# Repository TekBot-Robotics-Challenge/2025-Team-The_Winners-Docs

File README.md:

# TheWInners_Doc
Documentation des travaux de l'équipe les WInners participant à la TRC2025. 

## 🚀 Step-by-Step Getting Started Guide

### Step 1: Clone and Install

First, clone the repository and install dependencies:

```bash
# Clone the repository
git clone https://github.com/Marzoukath/TheWInners_Doc.git
cd TheWInners_Doc

# Install dependencies
yarn install

# Start development server
yarn dev
```

Your site will be available at `http://localhost:4321`

### Step 2: Configure Your Site

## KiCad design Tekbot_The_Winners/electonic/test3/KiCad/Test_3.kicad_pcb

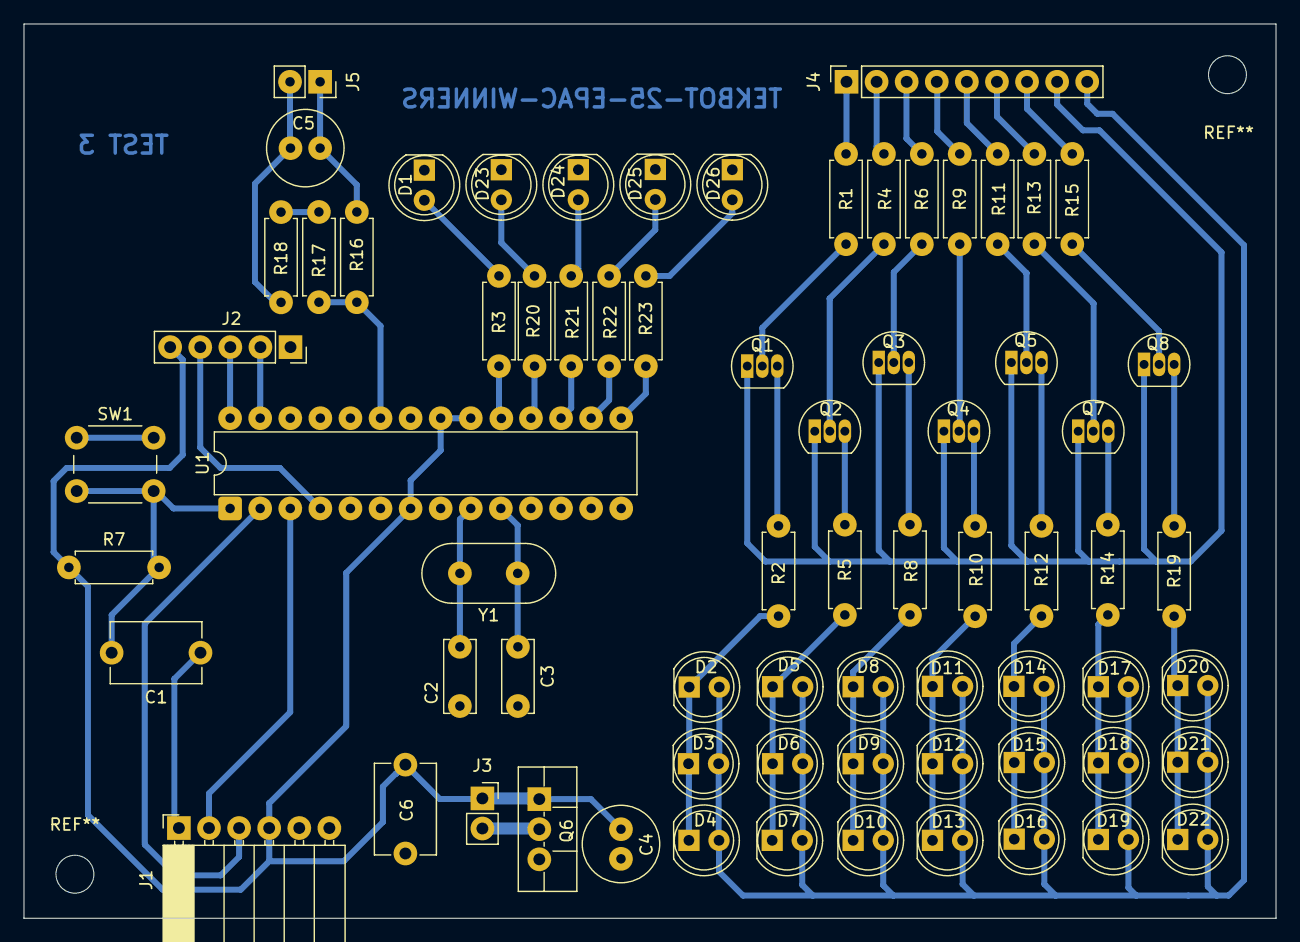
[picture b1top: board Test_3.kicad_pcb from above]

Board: 2 copper layers, 105.7 x 75.5 mm, 71 parts (0 on the bottom side), 56 nets.

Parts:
C1: 100nF; C_Disc_D7.5mm_W5.0mm_P7.50mm
C2, C3: 22pF; C_Disc_D6.0mm_W2.5mm_P5.00mm
C4, C5: 470µF; C_Radial_D6.3mm_H5.0mm_P2.50mm
C6: 100n; C_Disc_D7.5mm_W5.0mm_P7.50mm
D1, D2, D3, D4, D5, D6, D7, D8, D9, D10, D11, D12, D13, D14, D15, D16, D17, D18, D19, D20, D21, D22, D23, D24, D25, D26: LED; LED_D5.0mm
J1: Prog_connector; PinSocket_1x06_P2.54mm_Horizontal
J2: Conn_01x05_Pin; PinSocket_1x05_P2.54mm_Vertical
J3: 5V_power_Pins; PinSocket_1x02_P2.54mm_Vertical
J4: LED_pwm_connector; PinSocket_1x09_P2.54mm_Vertical
J5: Batt_connector; PinSocket_1x02_P2.54mm_Vertical
Q1, Q2, Q3, Q4, Q5, Q7, Q8: 2N2219; TO-92_Inline
Q6: NMOS; TO-220F-3_Vertical
R1, R2, R4, R5, R6, R8, R9, R10, R11, R12, R13, R14, R15, R19, R20, R21, R22, R23: R; R_Axial_DIN0207_L6.3mm_D2.5mm_P7.62mm_Horizontal
R3: 220; R_Axial_DIN0207_L6.3mm_D2.5mm_P7.62mm_Horizontal
R7, R16, R17: 10k; R_Axial_DIN0207_L6.3mm_D2.5mm_P7.62mm_Horizontal
R18: 4.7k; R_Axial_DIN0207_L6.3mm_D2.5mm_P7.62mm_Horizontal
SW1: SW_Push; SW_PUSH_6mm
U1: ATmega328-P; DIP-28_W7.62mm
Y1: Crystal; Crystal_HC49-U_Vertical

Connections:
/B+: C5.1, J5.1, R16.1
/B-: C5.2, J5.2, R18.2
/L_GND: J4.8, Q1.1 (E), Q2.1 (E), Q3.1 (E), Q4.1 (E), Q5.1 (E), Q7.1 (E), Q8.1 (E)
/L_Vcc: D2.2 (A), D3.2 (A), D4.2 (A), D5.2 (A), D6.2 (A), D7.2 (A), D8.2 (A), D9.2 (A), D10.2 (A), D11.2 (A), D12.2 (A), D13.2 (A), D14.2 (A), D15.2 (A), D16.2 (A), D17.2 (A), D18.2 (A), D19.2 (A), D20.2 (A), D21.2 (A), D22.2 (A), J4.9
/sg1: J4.1, R1.1
/sg2: J4.2, R4.1
/sg3: J4.3, R6.1
/sg4: J4.4, R9.1
/sg5: J4.5, R11.1
/sg6: J4.6, R13.1
/sg7: J4.7, R15.1
A0: R16.2, R17.1, U1.23 (PC0)
GND: J3.2, Q6.2 (D)
L-25: R23.1, U1.15 (PB1)
L-50: R22.1, U1.16 (PB2)
L-75: R21.1, U1.17 (PB3)
L-100: R20.1, U1.18 (PB4)
Lbuilt: R3.1, U1.19 (PB5)
unnamed: D1.2 (A), R3.2
unnamed: D2.1 (K), D3.1 (K), D4.1 (K), R2.2
unnamed: D5.1 (K), D6.1 (K), D7.1 (K), R5.2
unnamed: D8.1 (K), D9.1 (K), D10.1 (K), R8.2
unnamed: D11.1 (K), D12.1 (K), D13.1 (K), R10.2
unnamed: D14.1 (K), D15.1 (K), D16.1 (K), R12.2
unnamed: D17.1 (K), D18.1 (K), D19.1 (K), R14.2
unnamed: D20.1 (K), D21.1 (K), D22.1 (K), R19.2
unnamed: D23.2 (A), R20.2
unnamed: D24.2 (A), R21.2
unnamed: D25.2 (A), R22.2
unnamed: D26.2 (A), R23.2
unnamed: C1.1, J1.1
unnamed: Q1.2 (B), R1.2
unnamed: Q1.3 (C), R2.1
unnamed: Q2.2 (B), R4.2
unnamed: Q2.3 (C), R5.1
unnamed: Q3.2 (B), R6.2
unnamed: Q3.3 (C), R8.1
unnamed: Q4.2 (B), R9.2
unnamed: Q4.3 (C), R10.1
unnamed: Q5.2 (B), R11.2
unnamed: Q5.3 (C), R12.1
unnamed: Q7.2 (B), R13.2
unnamed: Q7.3 (C), R14.1
unnamed: Q8.2 (B), R15.2
unnamed: Q8.3 (C), R19.1
unnamed: R17.2, R18.1
OE: J2.4, U1.4 (PD2)
RST: C1.2, R7.2, SW1.2, U1.1 (~RESET/PC6)
Rx: J1.2, U1.3 (PD1)
SCL: J2.3, U1.28 (PC5)
SDA: J2.2, U1.27 (PC4)
Tx: J1.3, U1.2 (PD0)
V+: C4.1, C6.1, J1.4, J2.5, J3.1, Q6.1 (G), R7.1, U1.7 (VCC), U1.20 (AVCC), U1.21 (AREF)
V-: C2.2, C3.2, C4.2, C6.2, D1.1 (K), D23.1 (K), D24.1 (K), D25.1 (K), D26.1 (K), J1.6, J2.1, Q6.3 (S), SW1.1, U1.8 (GND), U1.22 (GND)
XTAL1: C2.1, U1.9 (XTAL1/PB6), Y1.2
XTAL2: C3.1, U1.10 (XTAL2/PB7), Y1.1

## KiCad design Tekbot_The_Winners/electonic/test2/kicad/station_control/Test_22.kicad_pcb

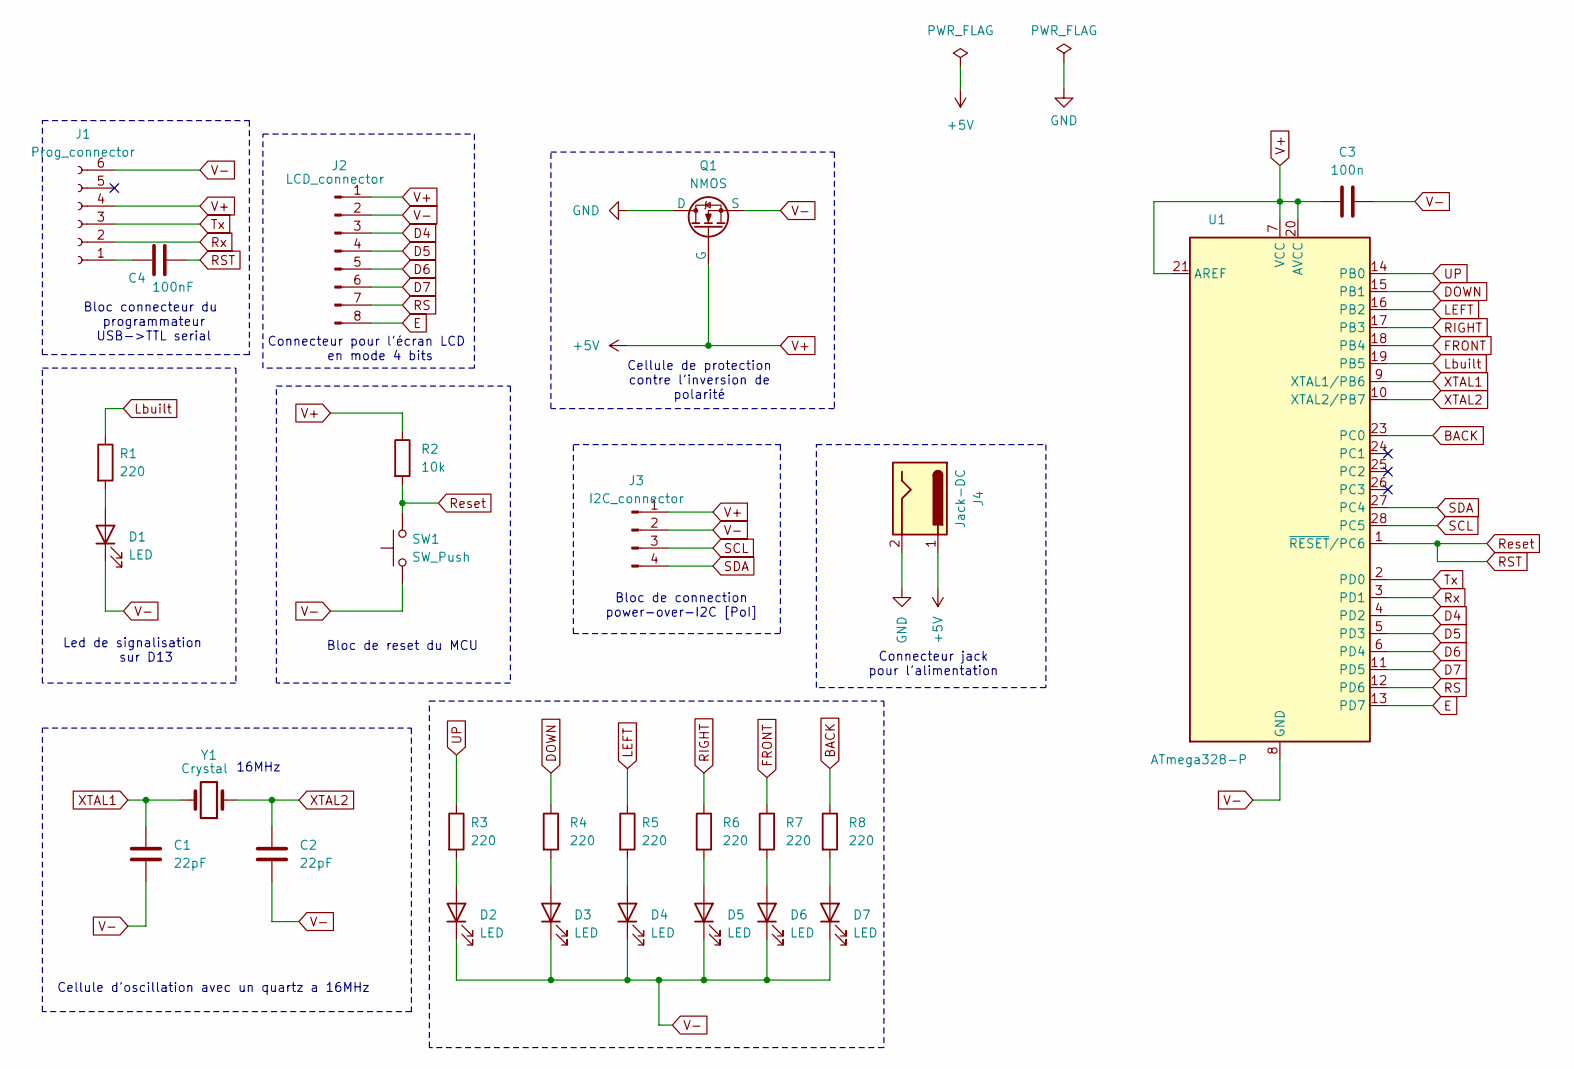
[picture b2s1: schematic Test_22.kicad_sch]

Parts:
C1, C2: 22pF; C_Disc_D7.5mm_W5.0mm_P7.50mm
C3: 100n; C_Disc_D7.5mm_W5.0mm_P7.50mm
C4: 100nF; C_Disc_D7.5mm_W5.0mm_P7.50mm
D1, D2, D3, D4, D5, D6, D7: LED; LED_D3.0mm
J1: Prog_connector; PinSocket_1x06_P2.54mm_Horizontal
J2: LCD_connector; PinSocket_1x08_P2.54mm_Vertical
J3: I2C_connector; JST_EH_S4B-EH_1x04_P2.50mm_Horizontal
J4: Jack-DC; BarrelJack_Horizontal
Q1: NMOS; TO-220F-3_Vertical
R1, R3, R4, R5, R6, R7, R8: 220; R_Axial_DIN0207_L6.3mm_D2.5mm_P7.62mm_Horizontal
R2: 10k; R_Axial_DIN0207_L6.3mm_D2.5mm_P7.62mm_Horizontal
SW1: SW_Push; SW_PUSH_6mm
U1: ATmega328-P; DIP-28_W7.62mm
Y1: Crystal; Crystal_HC49-U_Vertical

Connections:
BACK: R8.1, U1.23 (PC0)
D4: J2.3, U1.4 (PD2)
D5: J2.4, U1.5 (PD3)
D6: J2.5, U1.6 (PD4)
D7: J2.6, U1.11 (PD5)
DOWN: R4.1, U1.15 (PB1)
E: J2.8, U1.13 (PD7)
FRONT: R7.1, U1.18 (PB4)
GND: J4.2, Q1.1 (D)
LEFT: R5.1, U1.16 (PB2)
Lbuilt: R1.1, U1.19 (PB5)
unnamed: D1.2 (A), R1.2
unnamed: D2.2 (A), R3.2
unnamed: D3.2 (A), R4.2
unnamed: D4.2 (A), R5.2
unnamed: D5.2 (A), R6.2
unnamed: D6.2 (A), R7.2
unnamed: D7.2 (A), R8.2
unnamed: C4.1, J1.1
RIGHT: R6.1, U1.17 (PB3)
RS: J2.7, U1.12 (PD6)
RST: C4.2, R2.2, SW1.2, U1.1 (~RESET/PC6)
Rx: J1.2, U1.3 (PD1)
SCL: J3.3, U1.28 (PC5)
SDA: J3.4, U1.27 (PC4)
Tx: J1.3, U1.2 (PD0)
UP: R3.1, U1.14 (PB0)
V+: C3.1, J1.4, J2.1, J3.1, J4.1, Q1.2 (G), R2.1, U1.7 (VCC), U1.20 (AVCC), U1.21 (AREF)
V-: C1.2, C2.2, C3.2, D1.1 (K), D2.1 (K), D3.1 (K), D4.1 (K), D5.1 (K), D6.1 (K), D7.1 (K), J1.6, J2.2, J3.2, Q1.3 (S), SW1.1, U1.8 (GND), U1.22 (GND)
XTAL1: C1.1, U1.9 (XTAL1/PB6), Y1.2
XTAL2: C2.1, U1.10 (XTAL2/PB7), Y1.1

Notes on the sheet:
16MHz
Bloc connecteur du programmateur USB->TTL serial
Bloc de reset du MCU
Bloc de connection power-over-I2C [PoI]
Led de signalisation sur D13
Cellule d'oscillation avec un quartz a 16MHz
Connecteur jack pour l'alimentation
Cellule de protection contre l'inversion de polarité
Connecteur pour l'écran LCD en mode 4 bits

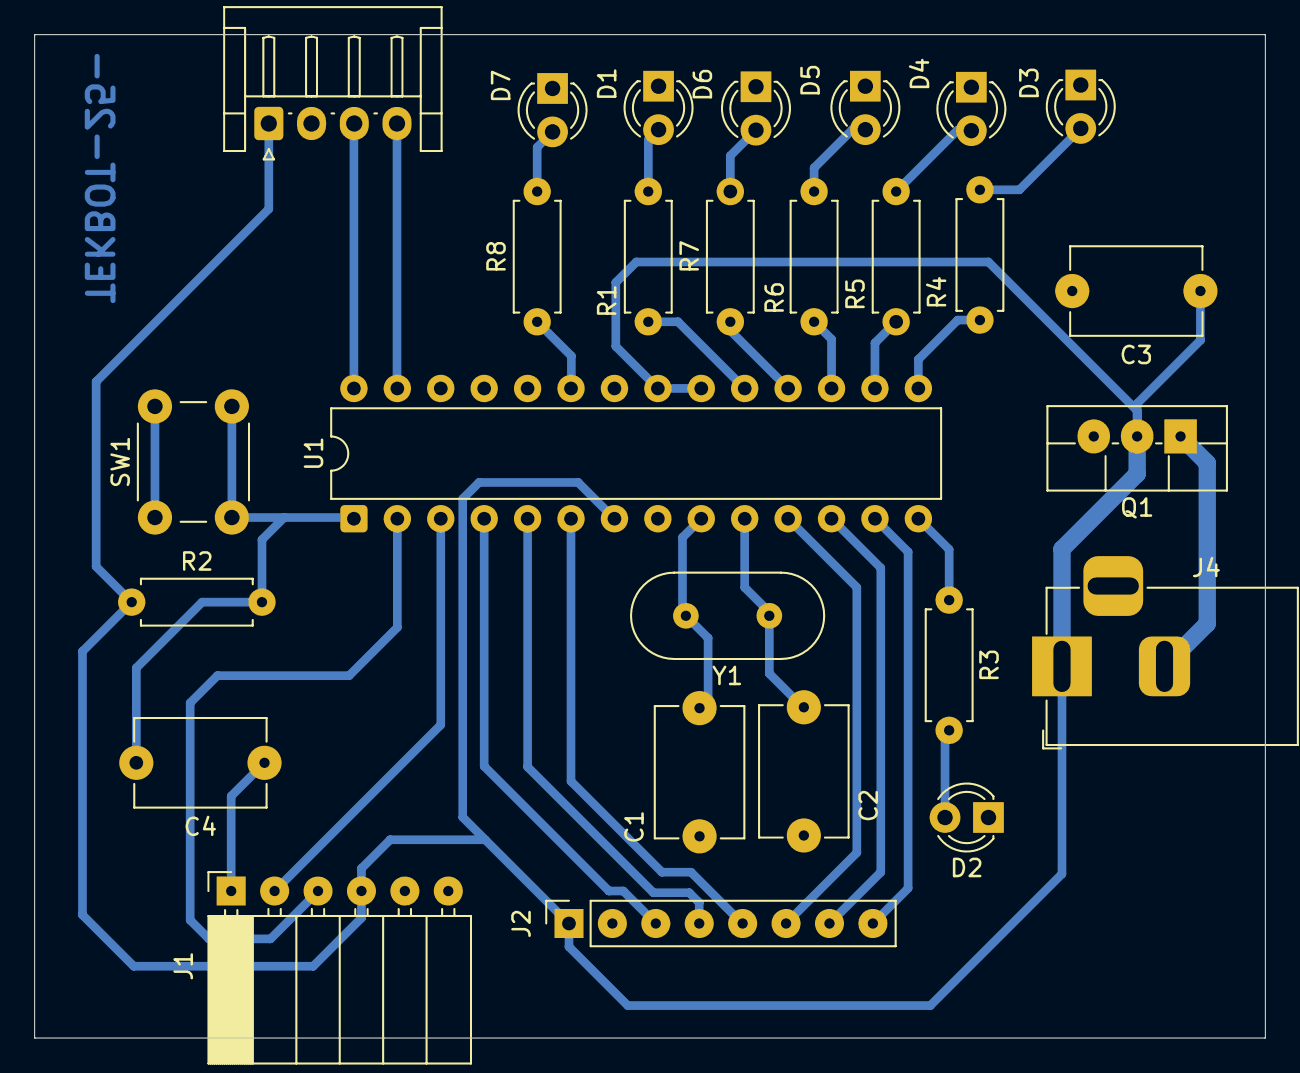
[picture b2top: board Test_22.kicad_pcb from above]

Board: 2 copper layers, 72.0 x 58.7 mm, 27 parts (0 on the bottom side), 31 nets.

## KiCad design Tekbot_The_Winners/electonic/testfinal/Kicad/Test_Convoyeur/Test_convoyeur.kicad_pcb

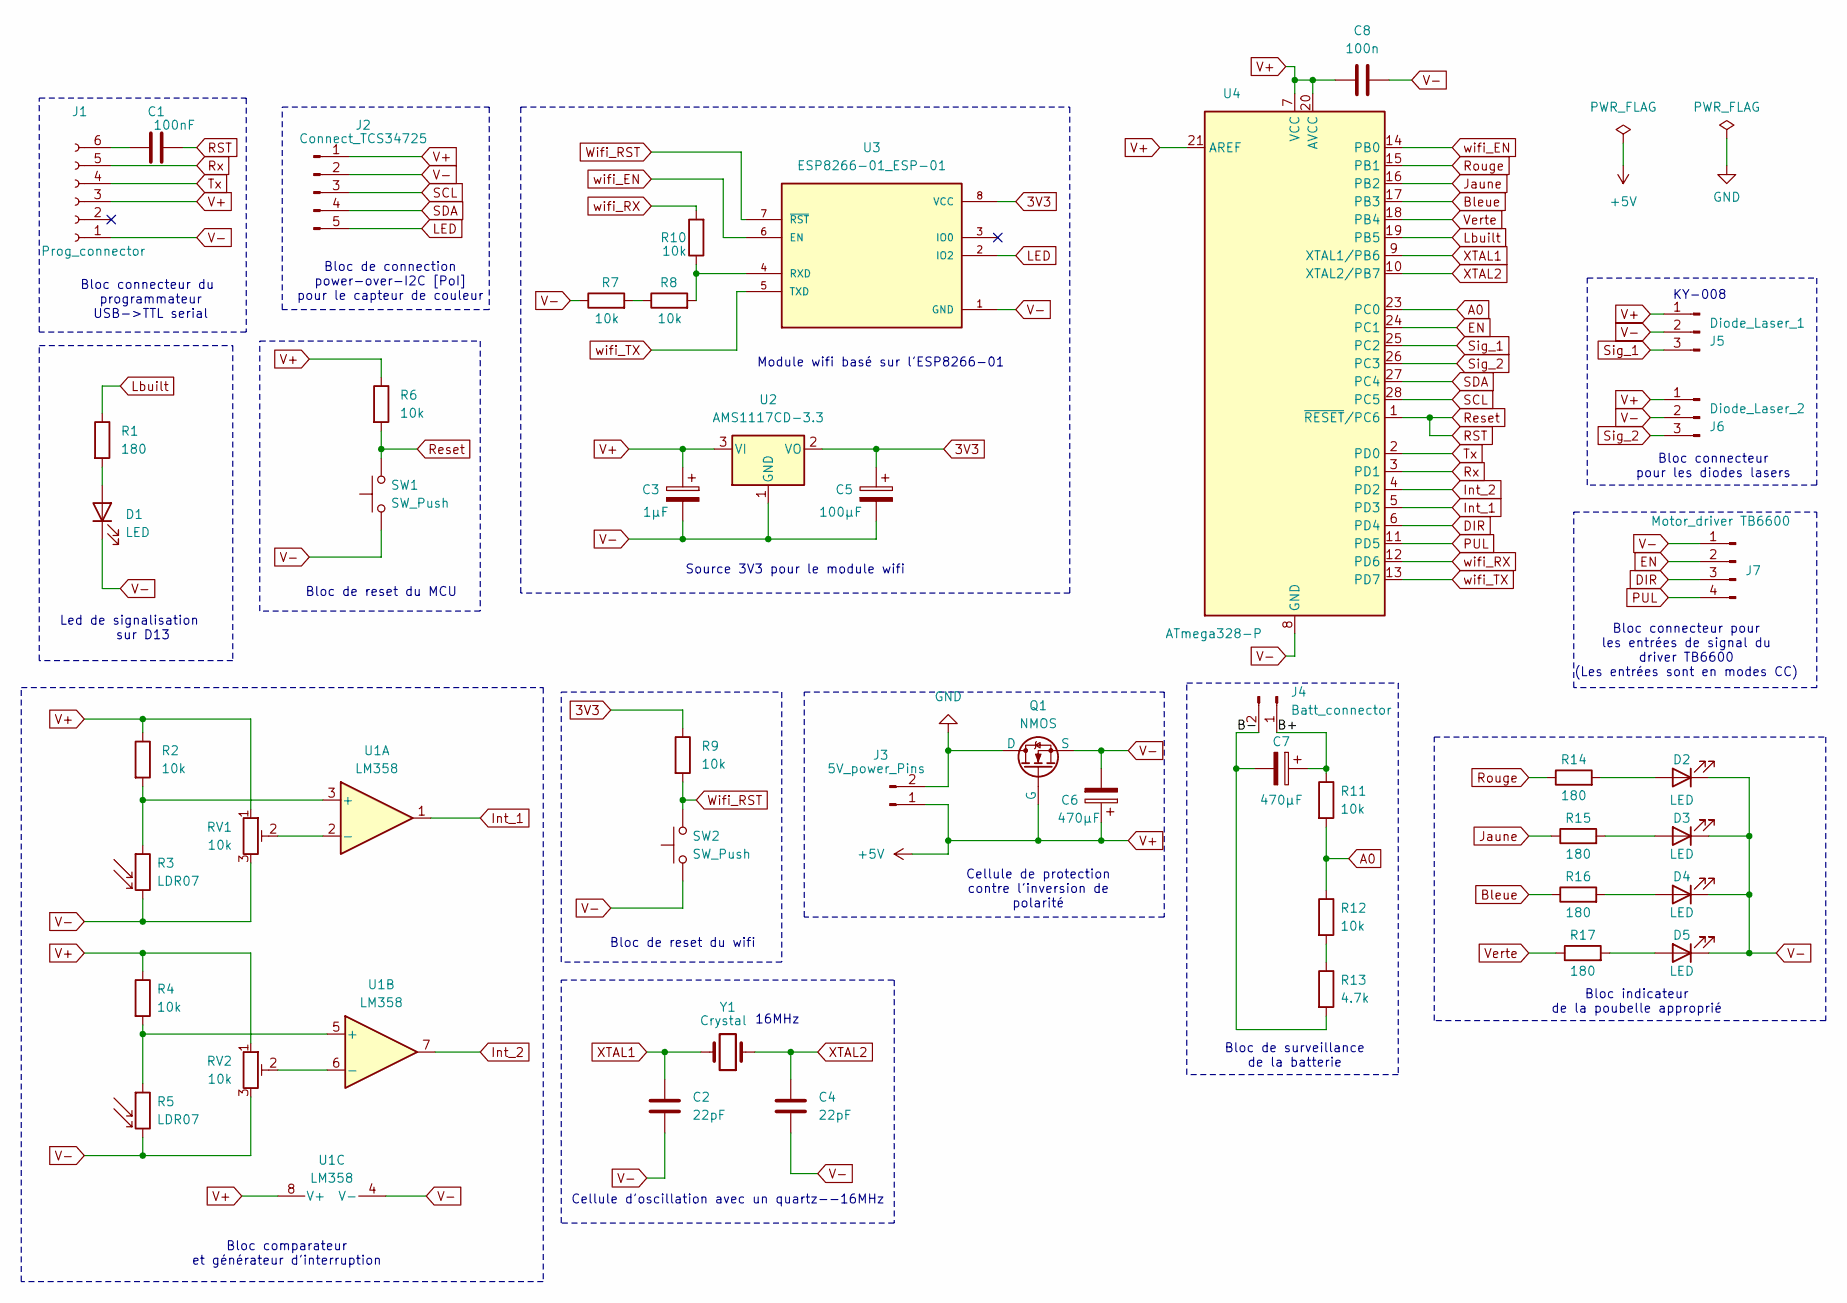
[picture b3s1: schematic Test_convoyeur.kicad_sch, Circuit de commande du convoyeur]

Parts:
C1: 100nF; C_Disc_D7.5mm_W5.0mm_P7.50mm
C2, C4: 22pF; C_Disc_D6.0mm_W2.5mm_P5.00mm
C3: 1µF; C_Radial_D6.3mm_H5.0mm_P2.50mm
C5: 100µF; C_Radial_D6.3mm_H5.0mm_P2.50mm
C6, C7: 470µF; C_Radial_D6.3mm_H5.0mm_P2.50mm
C8: 100n; C_Disc_D7.5mm_W5.0mm_P7.50mm
D1, D2, D3, D4, D5: LED; LED_D5.0mm
J1: Prog_connector; PinSocket_1x06_P2.54mm_Horizontal
J2: Connect_TCS34725; PinSocket_1x05_P2.54mm_Vertical
J3: 5V_power_Pins; PinSocket_1x02_P2.54mm_Vertical
J4: Batt_connector; PinSocket_1x02_P2.54mm_Vertical
J5: Diode_Laser_1; PinSocket_1x03_P2.54mm_Vertical
J6: Diode_Laser_2; PinSocket_1x03_P2.54mm_Vertical
J7: Motor_driver TB6600; PinHeader_1x04_P2.54mm_Vertical
Q1: NMOS; TO-220F-3_Vertical
R1, R14, R15, R16, R17: 180; R_Axial_DIN0207_L6.3mm_D2.5mm_P10.16mm_Horizontal
R2, R4, R6, R7, R8, R9, R10, R11, R12: 10k; R_Axial_DIN0207_L6.3mm_D2.5mm_P10.16mm_Horizontal
R3, R5: LDR07; R_LDR_5.1x4.3mm_P3.4mm_Vertical
R13: 4.7k; R_Axial_DIN0207_L6.3mm_D2.5mm_P10.16mm_Horizontal
RV1, RV2: 10k; R_ajustable
SW1, SW2: SW_Push; SW_PUSH_6mm
U1: LM358; DIP-8_W7.62mm
U2: AMS1117CD-3.3; TO-252-3_TabPin2
U3: ESP8266-01_ESP-01; XCVR_ESP8266-01_ESP-01; PARTREV V1.2
U4: ATmega328-P; DIP-28_W7.62mm
Y1: Crystal; Crystal_HC49-U_Vertical

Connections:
3V3: C5.1, R9.1, U2.2 (VO), U3.8 (VCC)
/B+: C7.1, J4.1, R11.1
/B-: C7.2, J4.2, R13.2
A0: R11.2, R12.1, U4.23 (PC0)
Bleue: R16.1, U4.17 (PB3)
DIR: J7.3, U4.6 (PD4)
EN: J7.2, U4.24 (PC1)
GND: J3.2, Q1.2 (D)
Int_1: U1.1, U4.5 (PD3)
Int_2: U1.7, U4.4 (PD2)
Jaune: R15.1, U4.16 (PB2)
LED: J2.5, U3.2 (IO2)
Lbuilt: R1.1, U4.19 (PB5)
unnamed: D1.2 (A), R1.2
unnamed: D2.2 (A), R14.2
unnamed: D3.2 (A), R15.2
unnamed: D4.2 (A), R16.2
unnamed: D5.2 (A), R17.2
unnamed: C1.1, J1.6
unnamed: R7.2, R8.1
unnamed: R12.2, R13.1
unnamed: R2.2, R3.1, U1.3 (+)
unnamed: RV1.2, U1.2 (-)
unnamed: R4.2, R5.1, U1.5 (+)
unnamed: RV2.2, U1.6 (-)
unnamed: R8.2, R10.1, U3.4 (RXD)
PUL: J7.4, U4.11 (PD5)
RST: C1.2, R6.2, SW1.2, U4.1 (~RESET/PC6)
Rouge: R14.1, U4.15 (PB1)
Rx: J1.5, U4.3 (PD1)
SCL: J2.3, U4.28 (PC5)
SDA: J2.4, U4.27 (PC4)
Sig_1: J5.3, U4.25 (PC2)
Sig_2: J6.3, U4.26 (PC3)
Tx: J1.4, U4.2 (PD0)
V+: C3.1, C6.1, C8.1, J1.3, J2.1, J3.1, J5.1, J6.1, Q1.1 (G), R2.1, R4.1, R6.1, RV1.1, RV2.1, U1.8 (V+), U2.3 (VI), U4.7 (VCC), U4.20 (AVCC), U4.21 (AREF)
V-: C2.2, C3.2, C4.2, C5.2, C6.2, C8.2, D1.1 (K), D2.1 (K), D3.1 (K), D4.1 (K), D5.1 (K), J1.1, J2.2, J5.2, J6.2, J7.1, Q1.3 (S), R3.2, R5.2, R7.1, RV1.3, RV2.3, SW1.1, SW2.1, U1.4 (V-), U2.1 (GND), U3.1 (GND), U4.8 (GND), U4.22 (GND)
Verte: R17.1, U4.18 (PB4)
Wifi_RST: R9.2, SW2.2, U3.7 (~RST)
XTAL1: C2.1, U4.9 (XTAL1/PB6), Y1.2
XTAL2: C4.1, U4.10 (XTAL2/PB7), Y1.1
wifi_EN: U3.6 (EN), U4.14 (PB0)
wifi_RX: R10.2, U4.12 (PD6)
wifi_TX: U3.5 (TXD), U4.13 (PD7)

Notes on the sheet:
Cellule de protection contre l'inversion de polarité
Bloc de reset du MCU
Bloc connecteur pour les entrées de signal du driver TB6600 (Les entrées sont en modes CC)
Bloc comparateur et générateur d'interruption
Source 3V3 pour le module wifi
Bloc indicateur de la poubelle approprié
Bloc de reset du wifi
Module wifi basé sur l'ESP8266-01
16MHz
KY-008
Bloc de surveillance de la batterie
Led de signalisation sur D13
Bloc connecteur pour les diodes lasers
Bloc de connection power-over-I2C [PoI] pour le capteur de couleur
Bloc connecteur du programmateur USB->TTL serial
Cellule d'oscillation avec un quartz--16MHz

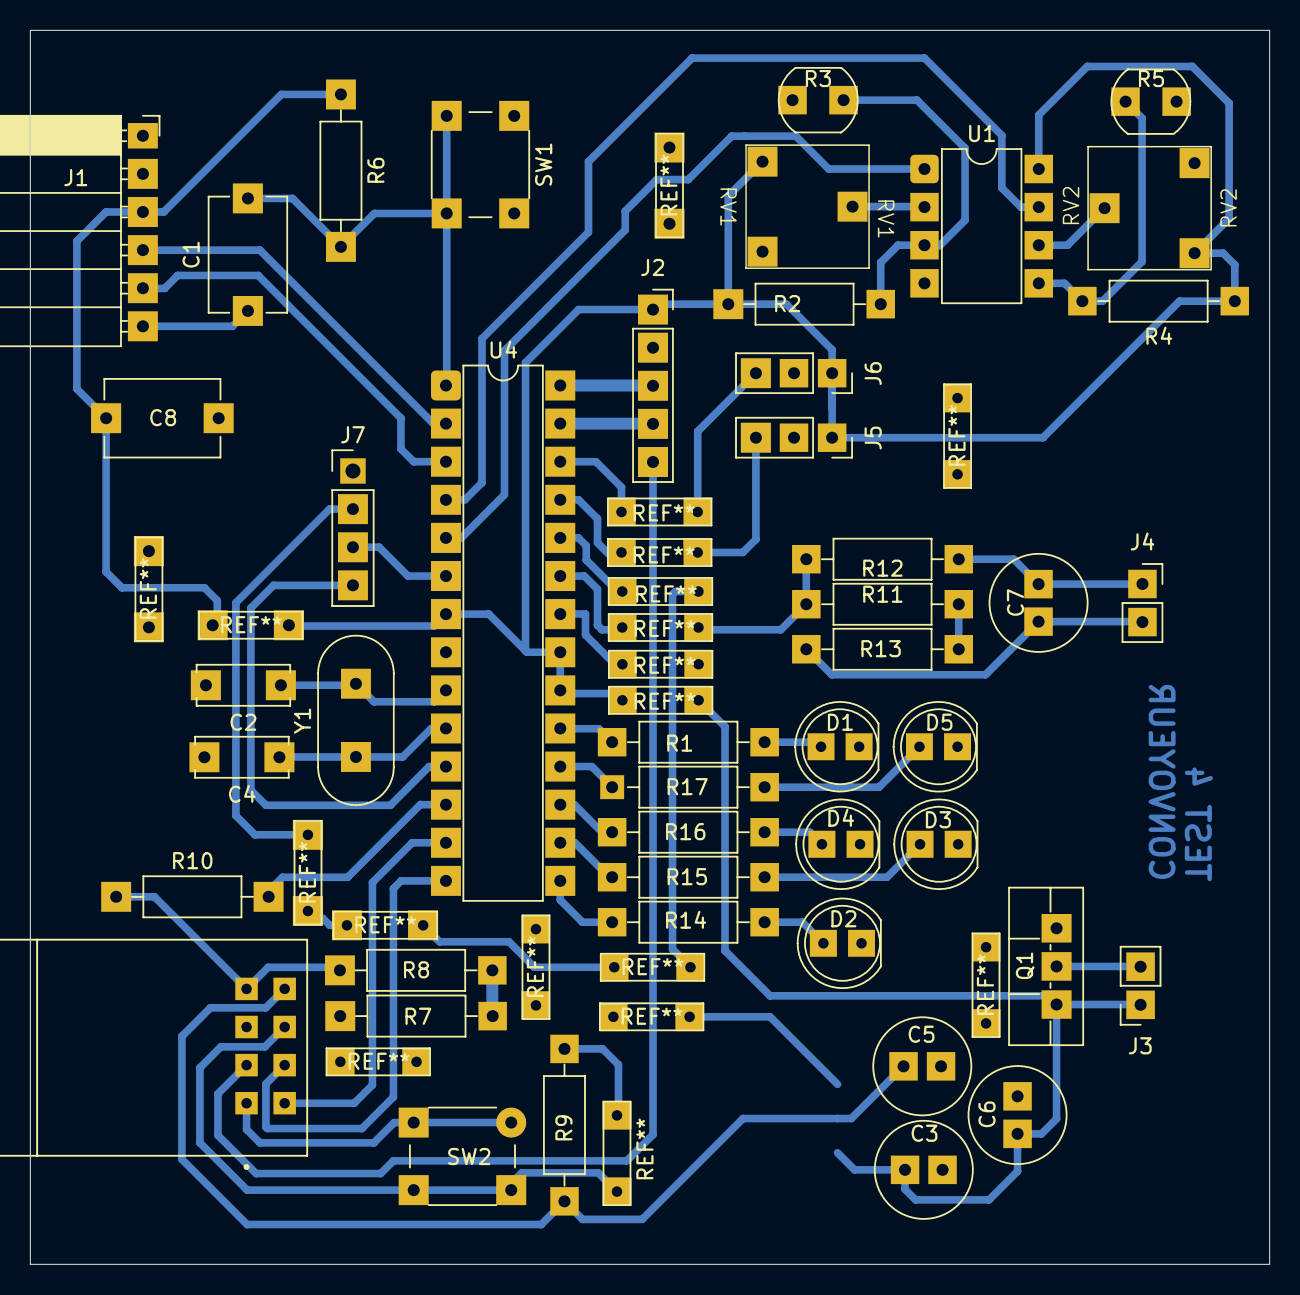
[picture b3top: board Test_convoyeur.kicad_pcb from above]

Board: 2 copper layers, 82.6 x 82.2 mm, 47 parts (1 on the bottom side), 44 nets.

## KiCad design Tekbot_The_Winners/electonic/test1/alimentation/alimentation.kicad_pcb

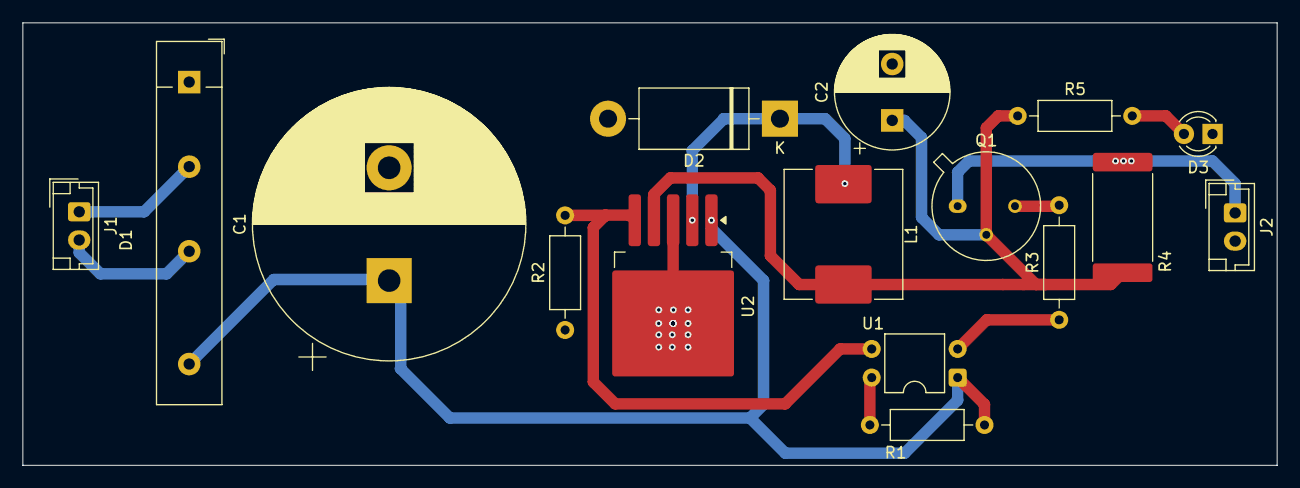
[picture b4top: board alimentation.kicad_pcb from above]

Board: 2 copper layers, 111.2 x 39.2 mm, 16 parts (0 on the bottom side), 12 nets.

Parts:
C1: 4700µF; CP_Radial_D24.0mm_P10.00mm_SnapIn
C2: 470µF; CP_Radial_D10.0mm_P5.00mm
D1: B40C5000-3x00A; Diode_Bridge_32.0x5.6x17.0mm_P10.0mm_P7.5mm
D2: 1N5822; D_DO-201AD_P15.24mm_Horizontal
D3: LED; LED_D3.0mm
J1: Input; JST_EH_B2B-EH-A_1x02_P2.50mm_Vertical
J2: Output; JST_EH_B2B-EH-A_1x02_P2.50mm_Vertical
L1: 33µH; L_Bourns_SRP1050WA
Q1: 2N2219; TO-39-3
R1, R2: 10k; R_Axial_DIN0207_L6.3mm_D2.5mm_P10.16mm_Horizontal
R3: 180; R_Axial_DIN0207_L6.3mm_D2.5mm_P10.16mm_Horizontal
R4: 350m; R_4020_10251Metric_Pad1.65x5.30mm_HandSolder
R5: 150; R_Axial_DIN0207_L6.3mm_D2.5mm_P10.16mm_Horizontal
U1: PC817; DIP-4_W7.62mm
U2: LM2596S-5; TO-263-5_TabPin3

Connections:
GND: C1.2, C2.2, D1.1 (-), D2.2 (A), D3.1 (K), J2.2, R2.1, U2.3 (GND)
unnamed: D2.1 (K), L1.1, U2.2 (OUT)
unnamed: D3.2 (A), R5.2
unnamed: Q1.3 (C), R3.2
unnamed: R1.1, U1.4
unnamed: R3.1, U1.2
S1: D1.2, J1.1
S2: D1.3, J1.2
Vin: C1.1, D1.4 (+), R1.2, U1.1, U2.1 (VIN)
Vo: C2.1, L1.2, Q1.2 (B), R4.1, R5.1, U2.4 (FB)
Von_off: R2.2, U1.3, U2.5 (~ON/OFF)
Vout: J2.1, Q1.1 (E), R4.2

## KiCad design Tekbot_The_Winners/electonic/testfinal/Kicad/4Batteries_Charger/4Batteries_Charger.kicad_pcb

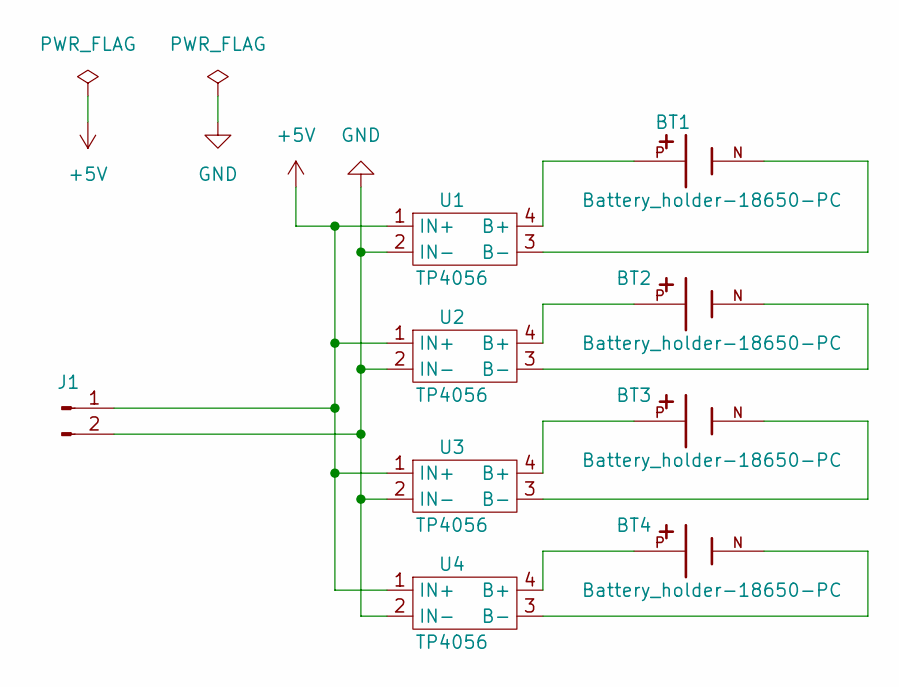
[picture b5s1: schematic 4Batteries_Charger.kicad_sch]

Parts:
BT1, BT2, BT3, BT4: Battery_holder-18650-PC; BAT_holder-18650-PC; PARTREV 05/17/19
J1: Conn_01x02_Pin; JST_EH_B2B-EH-A_1x02_P2.50mm_Vertical
U1, U2, U3, U4: TP4056; TP4056_module

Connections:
+5V: J1.1, U1.1 (IN+), U2.1 (IN+), U3.1 (IN+), U4.1 (IN+)
GND: J1.2, U1.2 (IN-), U2.2 (IN-), U3.2 (IN-), U4.2 (IN-)
unnamed: BT1.P, U1.4 (B+)
unnamed: BT1.N, U1.3 (B-)
unnamed: BT2.P, U2.4 (B+)
unnamed: BT2.N, U2.3 (B-)
unnamed: BT3.P, U3.4 (B+)
unnamed: BT3.N, U3.3 (B-)
unnamed: BT4.P, U4.4 (B+)
unnamed: BT4.N, U4.3 (B-)

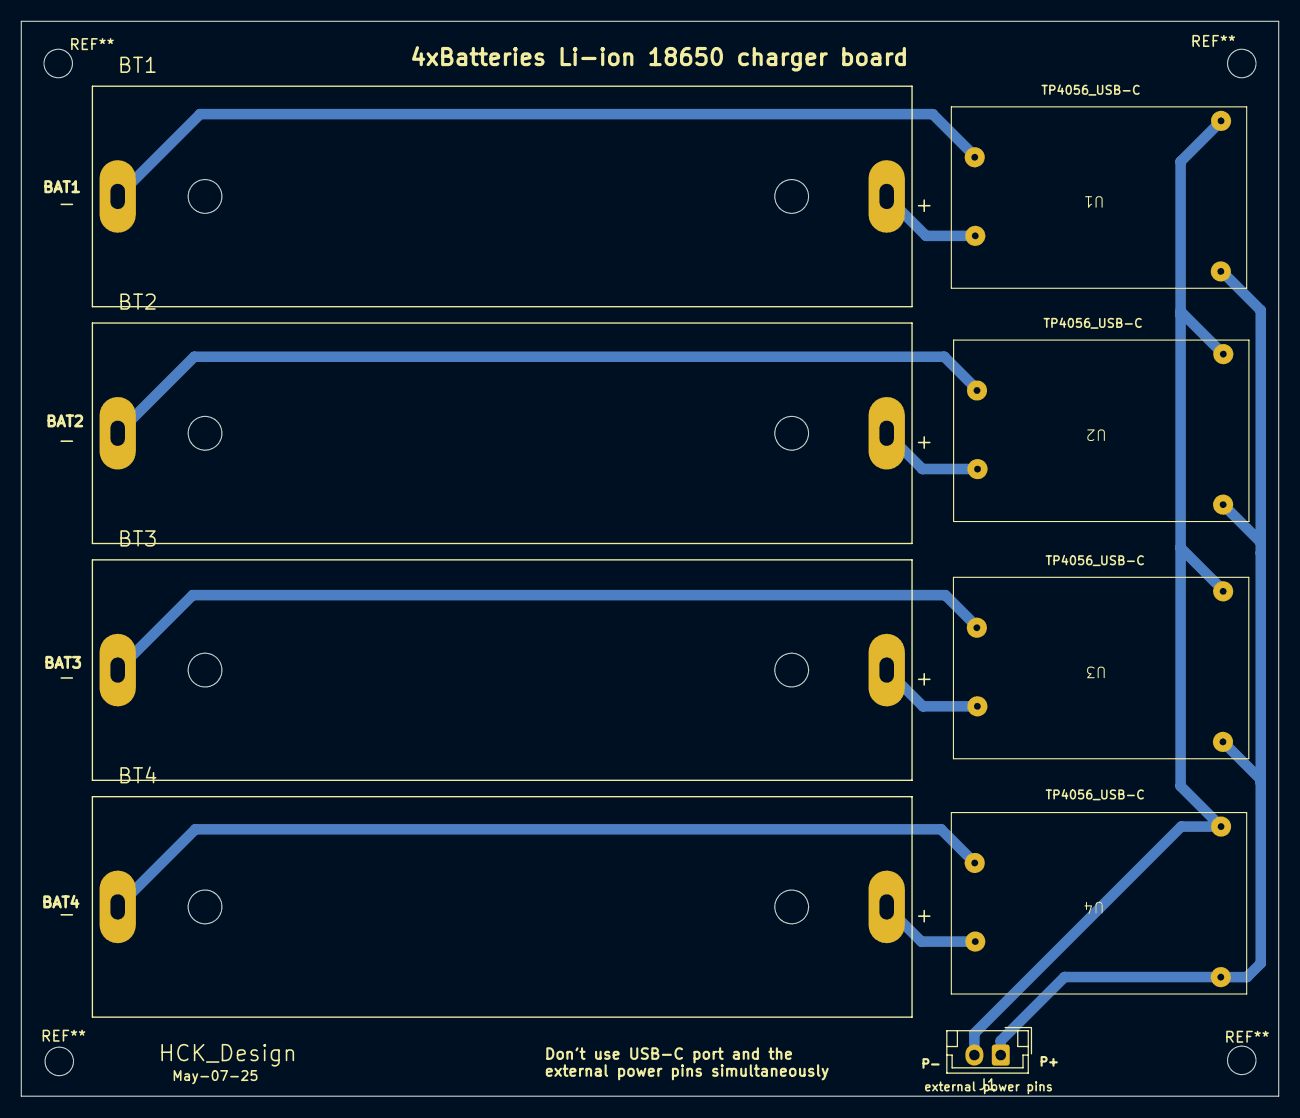
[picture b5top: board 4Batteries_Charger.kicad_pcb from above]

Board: 2 copper layers, 119.2 x 101.9 mm, 9 parts (0 on the bottom side), 10 nets.

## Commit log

2025-06-11 Initial Docusaurus project: Tekbot
2025-06-11 Add GitHub Pages deploy workflow
2025-06-11 Ajout du fichier deploy.yml pour déploiement GitHub Pages
2025-06-11 Déclenchement du workflow GitHub Pages
2025-06-11 Relance le workflow GitHub Actions
2025-06-11 Relance le workflow GitHubn Actions
2025-06-11 Corrige le fichier deploy.yml pour GitHub Actions
2025-06-11 Ajout option clean pour déploiement gh-pages
2025-06-11 Fix deploy.yml: add force_orphan to avoid git conflicts
2025-06-11 Add force: true to actions-gh-pages
2025-06-12 Déploiement du site sur gh-pages
2025-06-12 Deploy website - based on b06320dd13b31b7d8d4deafd82d30f69f44d3b9e
2025-06-18 Ajout du dossier Tekbot_The_Winners
2025-06-18 Ajout 2 du dossier Tekbot_The_Winners
2025-06-18 Mise à jour 2 du dossier Tekbot_The_Winners
2025-06-22 Mise à jour
2025-06-28 Mise à jour du dossier Tekbot_The_Winners
2025-07-26 Push
2025-07-28 Download
2025-07-28 Ajout fichier
2025-07-30 Fichier step
2025-09-21 ajout de zip
2025-09-21 ajout
2025-10-10 tekbot docs
2026-01-14 AJOUTEZ
2026-01-15 Deploy Astro site to gh-pages
2026-01-15 les photos
2026-01-15 fix: add base path to all markdown images and links via remark plugin
2026-01-16 Change deployment branch to 'gh-pages'
2026-01-16 version en ligne fonctionnelle
2026-01-16 tt est fonctionnel
2026-01-16 changement de branche de deploiement
